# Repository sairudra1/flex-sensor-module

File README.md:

## 🌟 Flex Sensor Breakout Board  
### 🔧 Why This Design Is Better

## ❌ Problem with Traditional Flex Sensor Setup

In a conventional setup, a **flex sensor** must be used with an **external resistor** to form a **voltage divider**.  
The voltage divider output is then connected to the **ADC pin of a microcontroller** to measure the bending angle.

### ⚠️ Limitations of this approach:

- 🔩 Requires an external resistor  
  → Leads to messy breadboard wiring  

- 📉 Voltage divider dependency  
  → Causes analog noise and unstable readings  

- 🎯 ADC conversion issues  
  → Reduced accuracy on noisy or low-quality boards  

- 🧩 Extra external components  
  → Not beginner-friendly and increases complexity  

- 📦 Higher component count  
  → Increases BOM and chances of wiring errors  

## ✅ Why This Flex Sensor Breakout Board Is Better

This breakout board integrates the required circuitry directly onto the PCB, eliminating the need for external resistors and simplifying sensor interfacing.

### 🚀 Key Advantages:

- 🔌 No external resistor required  
- 🧹 Clean and compact wiring  
- 📊 Stable and noise-reduced output signal  
- 🧠 Beginner-friendly plug-and-play design  
- 🛠️ Optimized and reduced BOM  

> 📄 **Note:** The complete Bill of Materials (BOM) is included

this one is 4 layer pcb design

✅ How This Flex Sensor Breakout Board Fixes It
This breakout board integrates the necessary circuitry directly on the PCB so you don’t need an external resistor or ADC-based measurement.

You get:
🔌 Direct digital output (D0 pin)
📶 Output becomes HIGH or LOW depending on flex detection
🔄 On-board selector/jumper to choose active-high or active-low output
🚫 No analog signal → no noise issues
🧹 Cleaner wiring → perfect for beginners and compact projects
no longer have to build a noisy voltage divider on a breadboard.
Just plug in the flex sensor and read a clean digital signal — HIGH when flexed (or LOW, depending on your selection), and ready to be used in any microcontroller project.

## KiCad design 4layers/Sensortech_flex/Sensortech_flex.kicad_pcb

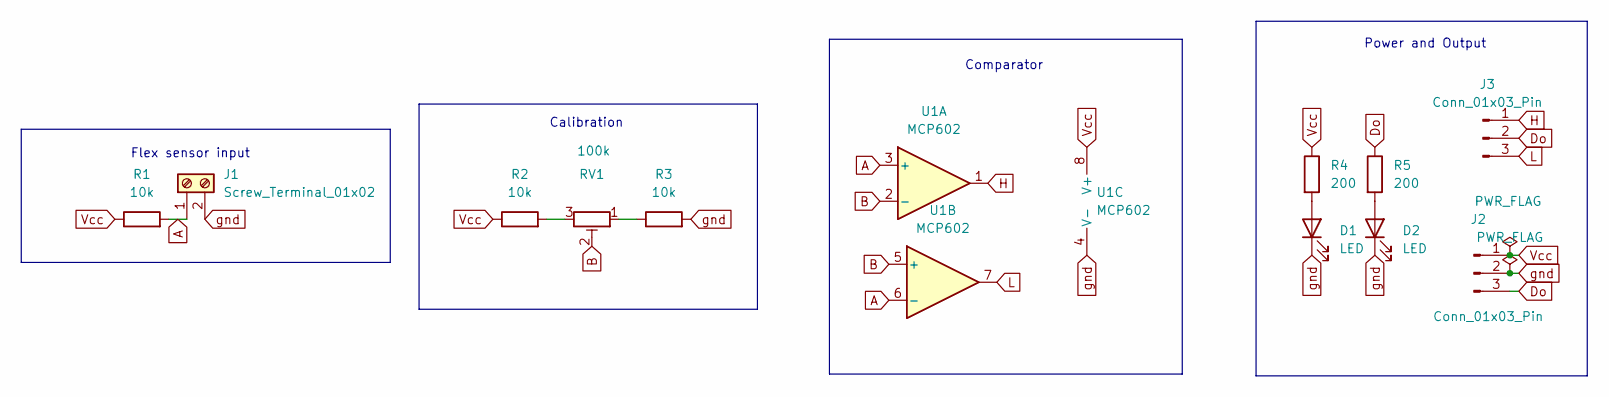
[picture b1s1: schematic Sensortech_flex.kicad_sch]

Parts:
D1, D2: LED; LED_0805_2012Metric_Pad1.15x1.40mm_HandSolder
J1: Screw_Terminal_01x02; TerminalBlock_Phoenix_MPT-0,5-2-2.54_1x02_P2.54mm_Horizontal
J2, J3: Conn_01x03_Pin; PinHeader_1x03_P2.54mm_Vertical
R1, R2, R3: 10k; R_0805_2012Metric_Pad1.20x1.40mm_HandSolder
R4, R5: 200; R_0805_2012Metric_Pad1.20x1.40mm_HandSolder
RV1: 100k; Potentiometer_Bourns_3386F_Vertical
U1: MCP602; DIP-8_W7.62mm

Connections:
A: J1.1, R1.2, U1.3 (+), U1.6 (-)
B: RV1.2, U1.2 (-), U1.5 (+)
Do: J2.3, J3.2, R5.1
H: J3.1, U1.1
L: J3.3, U1.7
unnamed: D1.2 (A), R4.2
unnamed: D2.2 (A), R5.2
unnamed: R2.2, RV1.3
unnamed: R3.1, RV1.1
Vcc: J2.1, R1.1, R2.1, R4.1, U1.8 (V+)
gnd: D1.1 (K), D2.1 (K), J1.2, J2.2, R3.2, U1.4 (V-)

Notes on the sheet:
Power and Output
Flex sensor input
Comparator
Calibration

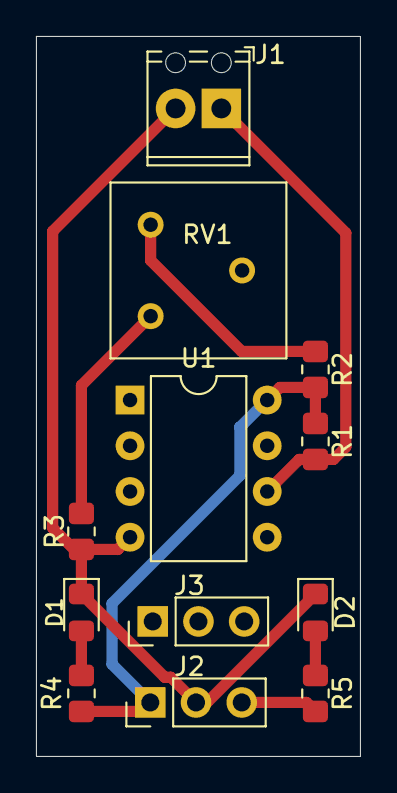
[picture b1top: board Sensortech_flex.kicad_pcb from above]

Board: 4 copper layers, 18.0 x 40.0 mm, 12 parts (0 on the bottom side), 11 nets.

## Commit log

2025-12-12 4 LAYER DESIGN
